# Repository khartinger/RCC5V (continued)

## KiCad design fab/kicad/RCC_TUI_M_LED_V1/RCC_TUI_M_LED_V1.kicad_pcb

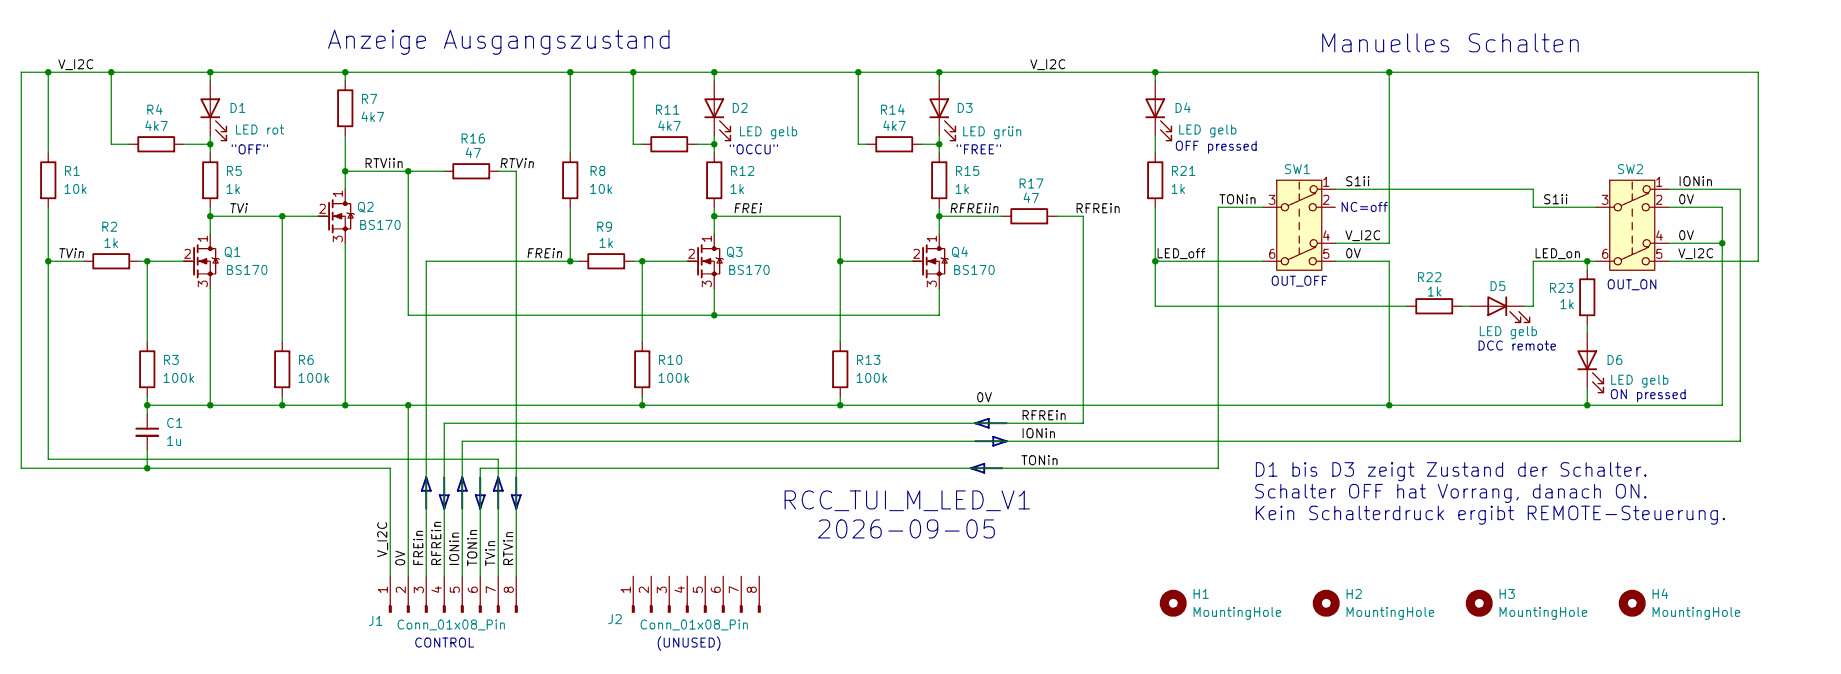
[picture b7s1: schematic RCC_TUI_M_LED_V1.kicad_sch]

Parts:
C1: 1u; C_L4mm_D3mm_P2.54mm_kh
D1: LED rot; LED_D3.0mm_kh
D2, D4, D5, D6: LED gelb; LED_D3.0mm_kh
D3: LED grün; LED_D3.0mm_kh
H1, H2, H3, H4: MountingHole; MountingHole_2.2mm_M2_Pad_TopBottom_kh
J1, J2: Conn_01x08_Pin; PinSocket_1x08_P2.54mm_Vertical_11mm_kh
Q1, Q2, Q3, Q4: BS170; TO-92_Inline_Wide_custom
R1: 10k; R_Axial_DIN0204_L3.6mm_D1.6mm_P2.54mm_Vertical
R2, R5, R9, R21, R22, R23: 1k; R_Axial_DIN0204_L3.6mm_D1.6mm_P2.54mm_Vertical_kh
R3, R6, R10, R13: 100k; R_Axial_DIN0204_L3.6mm_D1.6mm_P2.54mm_Vertical
R4, R11, R14: 4k7; R_Axial_DIN0204_L3.6mm_D1.6mm_P2.54mm_Vertical_kh
R7: 4k7; R_Axial_DIN0204_L3.6mm_D1.6mm_P2.54mm_Vertical
R8: 10k; R_Axial_DIN0204_L3.6mm_D1.6mm_P2.54mm_Vertical_kh
R12, R15: 1k; R_Axial_DIN0204_L3.6mm_D1.6mm_P2.54mm_Vertical
R16: 47; R_Axial_DIN0204_L3.6mm_D1.6mm_P3.81mm_Vertical_kh
R17: 47; R_Axial_DIN0207_L6.3mm_D2.5mm_P12.7mm_Horizontal_kh
SW1, SW2: SW_Push_DPDT_8x8

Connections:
/0V: C1.1, D6.1 (K), J1.2, Q1.3 (S), Q2.3 (S), R3.2, R6.2, R10.2, R13.2, SW1.5 (B), SW2.2 (B), SW2.4 (A)
/FREi: Q3.1 (D), Q4.2 (G), R12.2, R13.1
/FREin: J1.3, R8.2, R9.1
/IONin: J1.5, SW2.1 (A)
/LED_off: R21.2, R22.1, SW1.6 (C)
/LED_on: D5.1 (K), R23.1, SW2.6 (C)
/RFREiin: Q4.1 (D), R15.2, R17.1
/RFREin: J1.4, R17.2
/RTViin: Q2.1 (D), Q3.3 (S), Q4.3 (S), R7.2, R16.1
/RTVin: J1.8, R16.2
/S1ii: SW1.1 (A), SW2.3 (C)
/TONin: J1.6, SW1.3 (C)
/TVi: Q1.1 (D), Q2.2 (G), R5.2, R6.1
/TVin: J1.7, R1.2, R2.1
/V_I2C: C1.2, D1.2 (A), D2.2 (A), D3.2 (A), D4.2 (A), J1.1, R1.1, R4.1, R7.1, R8.1, R11.1, R14.1, SW1.4 (A), SW2.5 (B)
unnamed: D1.1 (K), R4.2, R5.1
unnamed: D2.1 (K), R11.2, R12.1
unnamed: D3.1 (K), R14.2, R15.1
unnamed: D4.1 (K), R21.1
unnamed: D5.2 (A), R22.2
unnamed: D6.2 (A), R23.2
unnamed: Q1.2 (G), R2.2, R3.1
unnamed: Q3.2 (G), R9.2, R10.1

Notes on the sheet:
ON pressed
(UNUSED)
OUT_OFF
"OCCU"
D1 bis D3 zeigt Zustand der Schalter. Schalter OFF hat Vorrang, danach ON. Kein Schalterdruck ergibt REMOTE-Steuerung.
Manuelles Schalten
"OFF"
CONTROL
OUT_ON
OFF pressed
Anzeige Ausgangszustand
"FREE"
RCC_TUI_M_LED_V1 2026-09-05
DCC remote
NC=off

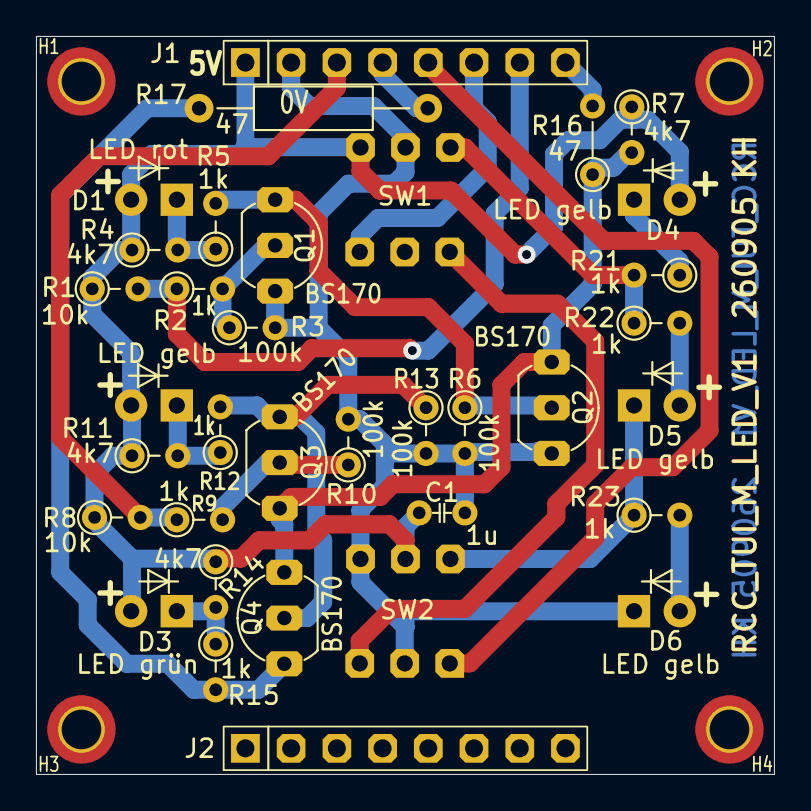
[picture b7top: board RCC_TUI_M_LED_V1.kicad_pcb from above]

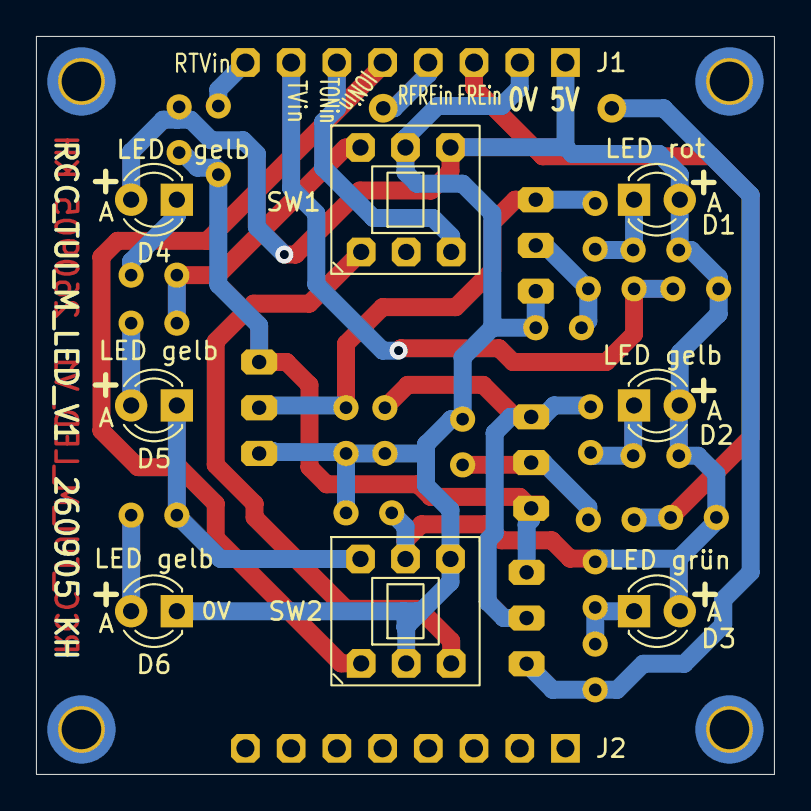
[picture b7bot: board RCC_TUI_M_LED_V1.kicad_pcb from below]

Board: 2 copper layers, 41.0 x 41.0 mm, 39 parts (8 on the bottom side), 23 nets.

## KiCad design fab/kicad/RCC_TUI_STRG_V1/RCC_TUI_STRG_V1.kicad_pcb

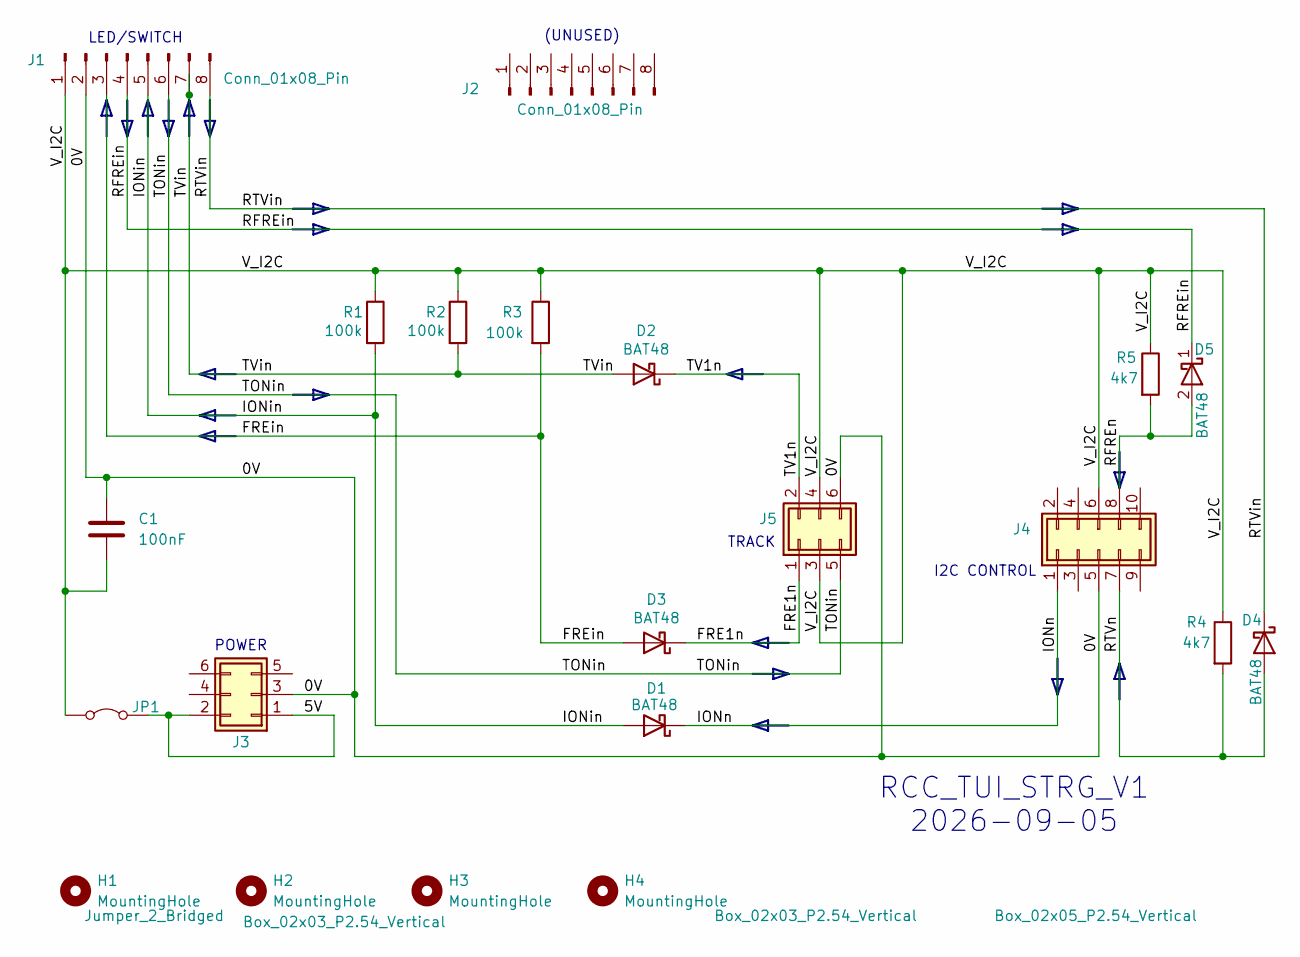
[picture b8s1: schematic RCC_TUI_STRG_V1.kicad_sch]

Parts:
C1: 100nF; C_Rect_L7.0mm_W2.0mm_P5.00mm_kh
D1, D2, D3, D4: BAT48; D_DO-35_P7.62mm_Horizontal_kh
D5: BAT48; D_DO-35_P12.7mm_Horizontal_kh
H1, H2, H3, H4: MountingHole; MountingHole_2.2mm_M2_Pad_TopBottom_kh
J1, J2: Conn_01x08_Pin; PinSocket_1x08_P2.54mm_Vertical_kh
J3, J5: Box_02x03_P2.54_Vertical; Box_02x03_P2.54mm_Vertical_kh
J4: Box_02x05_P2.54_Vertical; Box_02x05_P2.54mm_Vertical_kh
JP1: Jumper_2_Bridged; SolderJumper-2_P1.3mm_Bridged_Pad1.0x1.5mm
R1: 100k; R_Axial_P5.08_Vertical_kh
R2, R3: 100k; R_Axial_DIN0204_L3.6mm_D1.6mm_P2.54mm_Vertical_kh
R4, R5: 4k7; R_Axial_DIN0204_L3.6mm_D1.6mm_P2.54mm_Vertical_kh

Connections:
/0V: C1.1, J1.2, J3.3, J4.5, J5.6
/5V: J3.1, J3.2, JP1.2 (B)
/FRE1n: D3.1 (K), J5.1
/FREin: D3.2 (A), J1.3, R3.2
/IONin: D1.2 (A), J1.5, R1.2
/IONn: D1.1 (K), J4.1
/RFREin: D5.1 (K), J1.4
/RFREn: D5.2 (A), J4.8, R5.2
/RTVin: D4.1 (K), J1.8
/RTVn: D4.2 (A), J4.7, R4.2
/TONin: J1.6, J5.5
/TV1n: D2.1 (K), J5.2
/TVin: D2.2 (A), J1.7, R2.2
/V_I2C: C1.2, J1.1, J4.6, J5.3, J5.4, JP1.1 (A), R1.1, R2.1, R3.1, R4.1, R5.1

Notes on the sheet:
TRACK
RCC_TUI_STRG_V1 2026-09-05
I2C CONTROL
POWER
(UNUSED)
LED/SWITCH

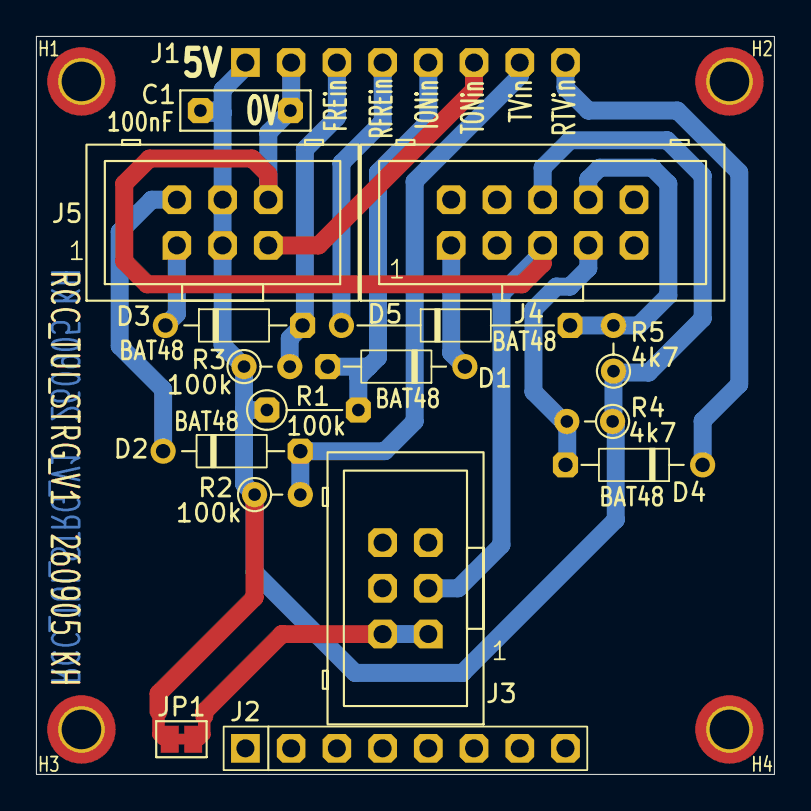
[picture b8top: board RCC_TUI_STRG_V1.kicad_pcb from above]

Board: 2 copper layers, 41.0 x 41.0 mm, 21 parts (1 on the bottom side), 14 nets.

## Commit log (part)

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2025-01-07 Add images
2025-01-12 Start building module 12
2025-01-12 Update module12
2025-01-29 Update Modul 12
2025-01-29 Update Module M12
2025-01-30 Update Modul M12
2025-01-30 Update Module 12
2025-02-05 Add Software Module 12
2025-02-08 Add Shield_I2C_5V_3V3_big
2025-02-09 Add 3D files
2025-02-12 Update 3d data
2025-02-12 rename /use to /examples
2025-02-12 move /kicad to fab/kicad
2025-02-16 Update rcc3_i2c
2025-02-22 Update kicad-Files
2025-03-04 Update kicad files
2025-03-05 Update RCC_5V_Parts
2025-03-06 Update kicad ..SUB25..
2025-03-07 Update LED config
2025-03-09 Update Parts
2025-03-12 Module01 created
2025-03-12 Update module M01
2025-03-13 Update Module 01
2025-03-15 Update M01
2025-03-20 Create Blocktester
2025-03-21 Update Blocktester odg
2025-03-28 Replace äöü
2025-03-30 New: Module 14
2025-03-31 Add 3d: turnout cover
2025-03-31 Update Module 14
2025-04-06 Update software module 14
2025-04-16 Add some PCBs
2025-04-27 Batch-Dateien für Module
2025-05-01 Update exampleTurnout2
2025-05-15 Update M7.md
    Update
2025-05-19 add zz_test
2025-06-01 Update LIESMICH
2025-06-05 Modul 13: liesmich.md
2025-06-14 Update module 13
2025-06-15 Update module m13
2025-06-18 Update Modul 13
2025-07-19 Update examples
2025-08-20 rename z_details to misc
2025-10-15 Add FreeCAD files
2025-10-15 update Bahnkoerper images
2025-10-15 Update "aufbau_bahnkoerper.png"
2025-10-19 Update Lichtraumprofil
2025-11-20 Add dust cover
2025-11-20 Add description dust cover
2025-11-21 Update dust_cover and freecad files
2026-01-04 Update rcc_demo1
2026-01-08 Update software/rcc_module12_V1
2026-01-08 Update software/rcc_module13_V1
2026-01-08 Update software/rcc_module14_V1
2026-01-08 Update rcc_module01_V1
2026-01-08 Add software/rcc_module10
2026-01-08 Add software/rcc_module11
2026-01-10 rcc_demo1: change WiFi data via mqtt
2026-01-10 Update rcc_module13 ESP32 software
2026-01-11 Update simplemqtt
2026-01-11 Update rcc_module11: simplemqtt+eeprom
2026-01-11 Update rss_module14
2026-01-11 New rcc_module01
2026-01-12 Update rcc_Module10
2026-02-24 Add RasPi_with_2yAP/LIESMICH.md
2026-02-24 add get mac, hostname
2026-03-27 Update Gleisrechner
2026-03-27 Add rcc_module01_V2 (Version 2026)
2026-04-27 Add ModulStütze Version 260427
